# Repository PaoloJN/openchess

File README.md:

<h1 align="center">OpenChess</h1>

<p align="center">
  A chessboard that knows where the pieces are.<br>
  64 Hall sensors, 81 RGB LEDs, one ESP32, a 3D-printed case, and a phone app.<br>
  Designed in KiCad, assembled by JLCPCB and by hand, built once, for one desk.
</p>

<p align="center">
  <a href="STATUS.md">Status</a> ·
  <a href="#how-it-works">How it works</a> ·
  <a href="#repository-map">Repo map</a> ·
  <a href="#build-notes">Build notes</a> ·
  <a href="#licenses">Licenses</a>
</p>

<p align="center">
  
  &nbsp;&nbsp;
  
</p>

---

## What this is

A one-off, hands-on learning project, built during my year-long internship at
UMD CPSE. I had never designed a PCB before this. The goal was never a
product. It was to get one physical board that:

- detects every piece on every square with a magnet under each piece,
- shows legal moves, hints, and errors with LEDs at the square corners,
- plays offline against its own chess engine with a little OLED menu,
- talks to a companion phone app over Bluetooth,
- lives in a clean printed case with a swappable top plate.

The first boards came back from JLCPCB in June 2026 and worked on the first
power-up. Everything since then has been firmware, the case, the app, and a
battery-module swap so it runs without a cable.

## See it work

<p align="center">
  
  &nbsp;&nbsp;&nbsp;
  
</p>

<p align="center">
  <sub>Left: the board under its wooden top, reacting to pieces. Right: first power-up of the bare matrix, one pixel walking the LED chain. Full-quality clip: <a href="docs/media/demo-pieces.mp4">demo-pieces.mp4</a>.</sub>
</p>

## How it works

**Sensing.** Each square has a DRV5032FC Hall-effect sensor under it. The
matrix is scanned one column at a time: the controller powers a column through
a TBD62783A high-side driver, then reads eight row lines. A full scan of the
board takes about 100 ms, fast enough to feel instant.

**Lights.** 81 WS2812B LEDs sit on the 9x9 grid of square corners, so one
square lights up as its four corners. The ESP32 drives the chain through a
74AHCT125 level shifter so the data line is a real 5 V signal. Frames go out
over I2S DMA so flash writes from Bluetooth cannot corrupt them mid-frame.

**Brain.** An ESP32 runs one non-blocking loop: sensor scan, game controller,
LED language, OLED menu, and a BLE server. The offline engine is a homebrew
alpha-beta search with quiescence, iterative deepening, piece-square tables,
and move ordering. It plays at a few selectable strengths and runs its own
native unit tests on the desktop.

**UI.** A 0.91" SSD1306 OLED and three buttons on the front wall of the case
for menus, plus a React Native app that pairs over BLE, mirrors the board,
streams moves, and controls the LEDs.

**Case.** Designed in Fusion 360 around the real PCB STEP exports. The walls
and front panel print as one part, the top plate is swappable between a
two-color printed chessboard and a laser-cut plexi top, and the back cover
clamps the PCB stack with heat-set inserts.

## Where things stand

| Area | State |
|---|---|
| Matrix board v0.1 | Built, all 64 sensors and 81 LEDs verified on hardware |
| Controller v0.1 | Built, works on USB. The stock battery module shuts its boost down under light load, so it is being replaced with a bq25185 charger/boost |
| Controller v2 | Shelved. An integrated ESP32-WROOM-32E, USB-C, charger, and boost design got as far as a clean schematic, then the v0.1 board proved good enough |
| Firmware | Integrated product build: OLED menu, offline AI, coaching lights, BLE. Desktop-tested, hardware verification ongoing |
| Companion app | Expo app, all screens built, real BLE pairing works end to end on an iPhone |
| Case | Final print package exported, corner test piece printed and iterated through v9 |
| Robot arm | Side quest: the board drives a Waveshare RoArm-M2-S over ESP-NOW, with a DIY servo gripper |

The detailed, dated list of next actions lives in [`STATUS.md`](STATUS.md).

## Repository map

```text
openchess/
├── hardware/
│   ├── hardware-board/          8x8 matrix PCB, 282 x 282 mm (KiCad, gerbers, JLC BOM/CPL)
│   ├── hardware-controller/     controller v0.1, DevKitC + Lipo Rider (frozen, boards exist)
│   ├── hardware-controller-v2/  shelved v2 design, schematic only, kept for reference
│   └── DESIGN_NOTES.md          design rationale and history for the v0.1 boards
├── firmware/                    PlatformIO ESP32 firmware: engine, UI, BLE, bench sketches
├── app/                         Expo / React Native companion app (BLE)
├── mechanical/                  Fusion 360 case, print package, plexi top, test pieces
├── firmware-roarm/              vendored RoArm-M2-S firmware with the gripper patch
├── docs/                        GPIO map, connector contracts, BOM, design specs
├── scripts/                     PDF tiling helpers, robot-arm console
└── references/                  upstream projects this builds on (git-ignored clones)
```

## Build notes

**Hardware.** Open the KiCad projects under `hardware/`. The v0.1 boards were
fabricated and SMD-assembled by JLCPCB using the Fabrication Toolkit plugin
exports in each board's `production/` folder. The DevKitC, Lipo Rider, column
driver, and connectors were hand-soldered.

**Firmware.**

```bash
cd firmware
pio run -e esp32dev -t upload      # the integrated product build
pio run -e bench_sensor -t upload  # or any bench sketch from src/bench/
pio test -e native_ai              # engine unit tests on the desktop
```

The GPIO map lives in `firmware/src/pins.h` and `docs/gpio-map.md`. On the
v0.1 controller the OLED shares the UART0 pins, so unplug the OLED to flash.

**App.**

```bash
cd app
npm install
npx expo run:ios        # BLE needs a native dev build, not Expo Go
```

**Case.** Print files and the screw list are in `mechanical/exports/README.md`.
Print the corner test piece first.

## Built on

- [joojoooo/OpenChess](https://github.com/joojoooo/OpenChess): the firmware
  started as an adaptation of this engine and board driver.
- [omercier01/Chessboard](https://github.com/omercier01/Chessboard): the v1
  board this rebuild started from.
- [waveshareteam/roarm_m2](https://github.com/waveshareteam/roarm_m2): the
  robot arm firmware, vendored with a small gripper patch.

## Licenses

| Part | License |
|---|---|
| Hardware (`hardware/`, `mechanical/`) | [CERN-OHL-S v2](LICENSE-hardware) |
| Firmware and app (`firmware/`, `app/`) | [MIT](LICENSE-firmware) |
| Documentation | [CC-BY-4.0](LICENSE-docs) |
| `firmware-roarm/` | Upstream Waveshare license, see its `LICENSE` |

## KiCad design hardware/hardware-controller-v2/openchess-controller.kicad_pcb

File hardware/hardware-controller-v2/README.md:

# hardware-controller-v2 (shelved)

**Status: shelved 2026-10-24, never fabricated.** The schematic reached
ERC-clean and layout was started. Dropped because the v0.1 controller with a
battery-module swap does the job for a one-off board. Kept for reference.

Integrated controller: soldered ESP32-WROOM-32E + USB-C (CH340C) + BQ24074
power-path charger + TPS61022 5V boost + AMS1117-3.3. Replaces the v1
DevKitC + Lipo Rider Plus daughterboards.

- Spec: `docs/superpowers/specs/2026-07-27-controller-v2-integrated-design.md`
- Plan: `docs/superpowers/plans/2026-07-27-controller-v2-integrated.md`
- GPIO map: `docs/gpio-map.md` (v2 table)
- Part sourcing + design values: `SOURCING.md`

The KiCad files keep their original names (`openchess-controller.*`) within this
directory; the directory name itself (`hardware-controller-v2/`) distinguishes v2
from frozen v1.

v1 (`../hardware-controller/`) is frozen — boards exist physically.

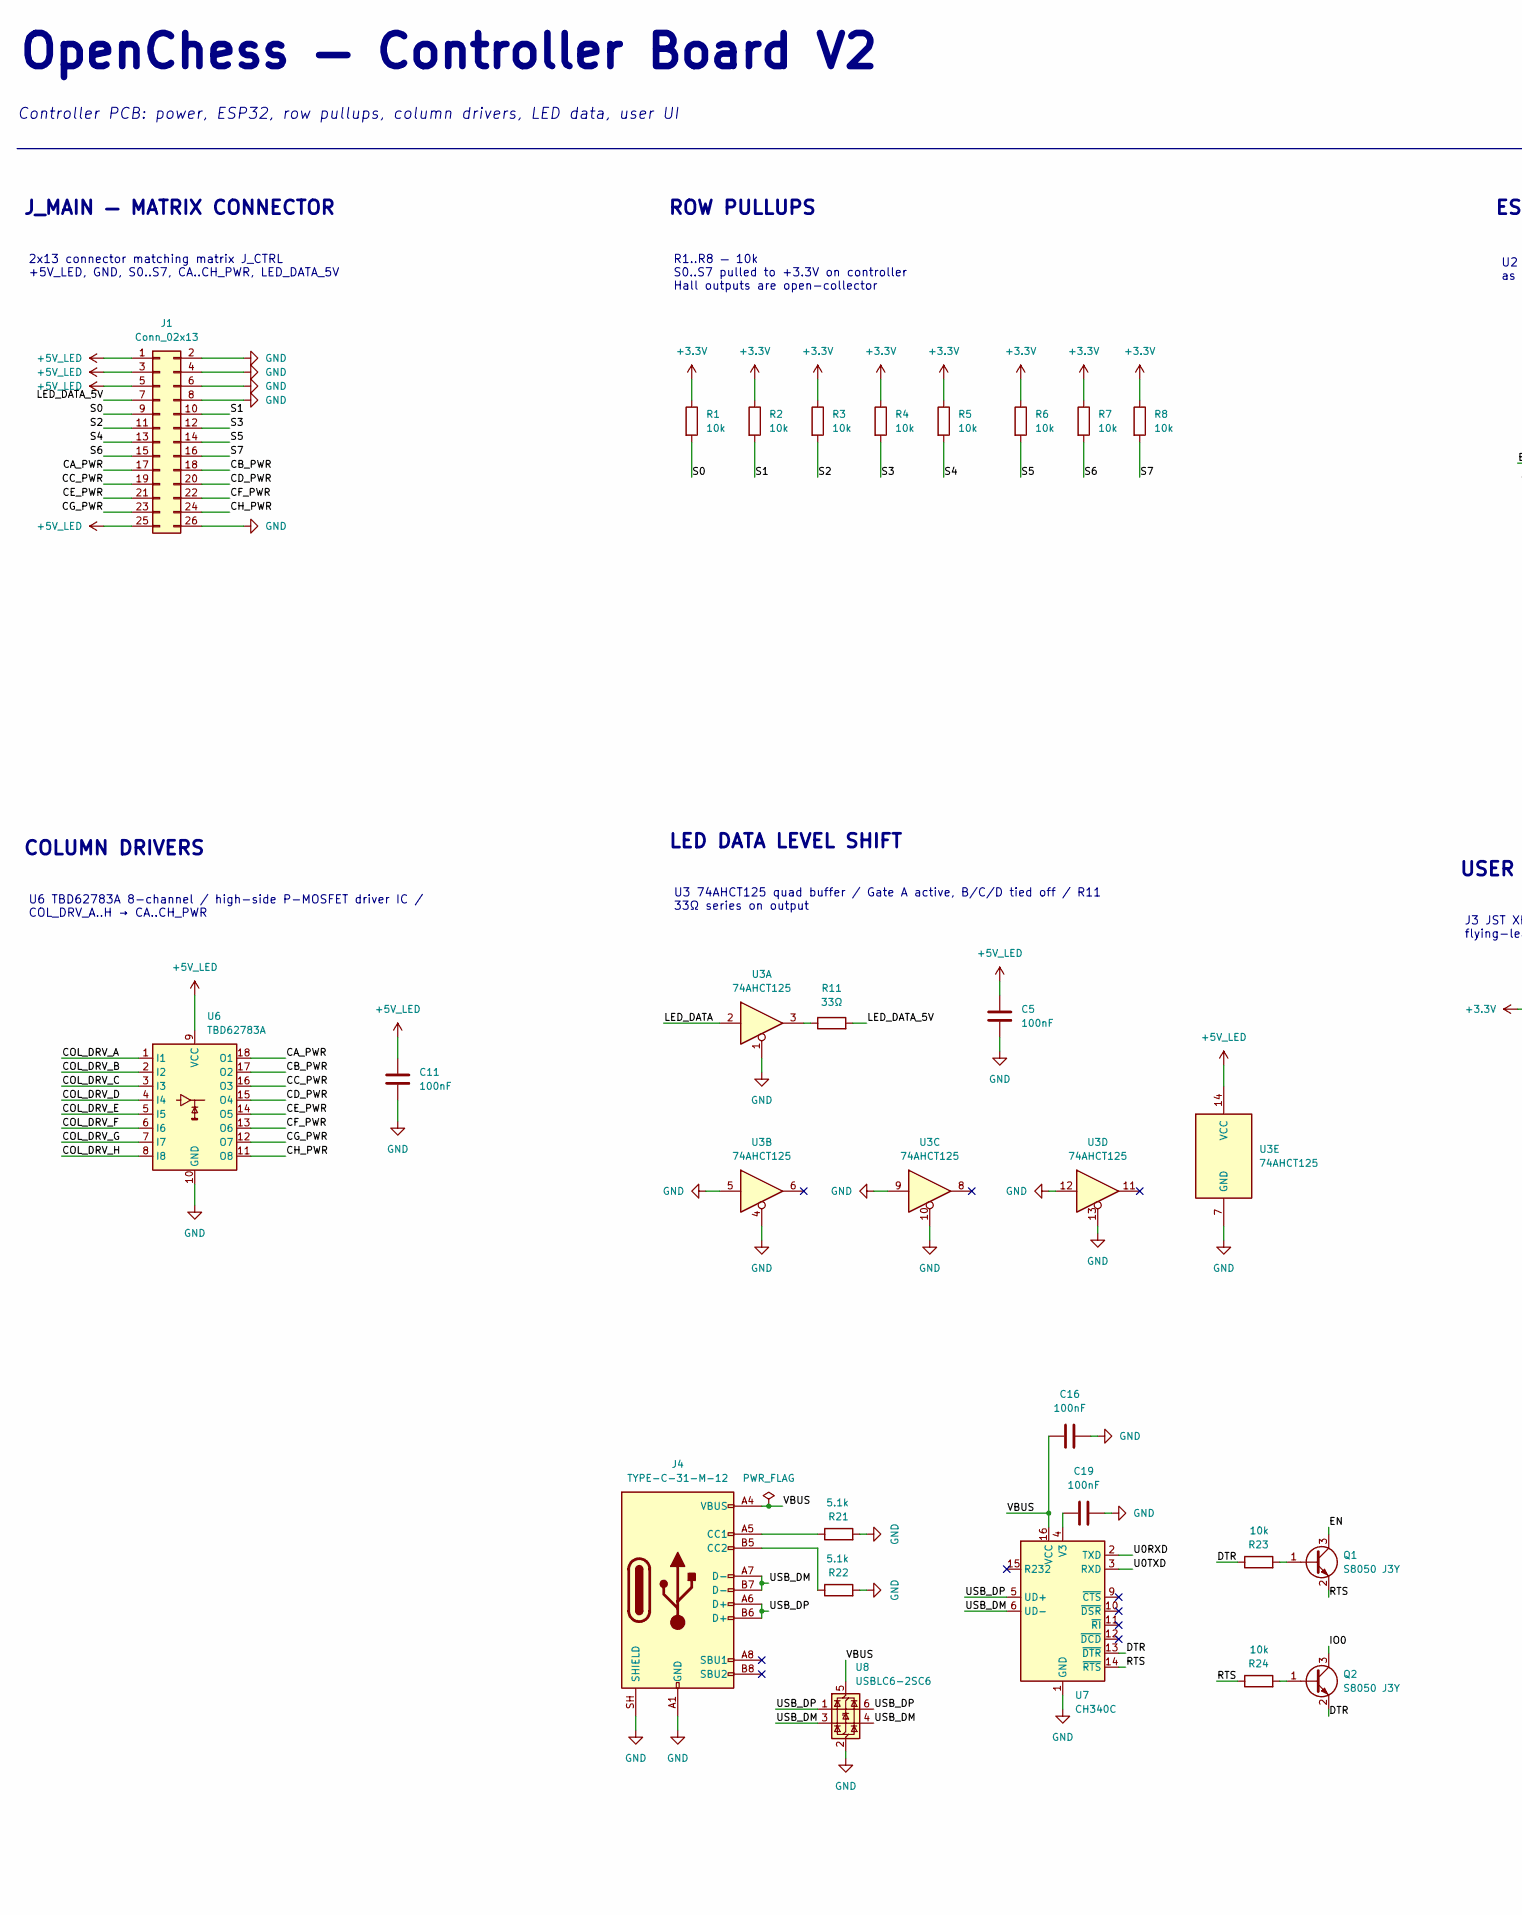
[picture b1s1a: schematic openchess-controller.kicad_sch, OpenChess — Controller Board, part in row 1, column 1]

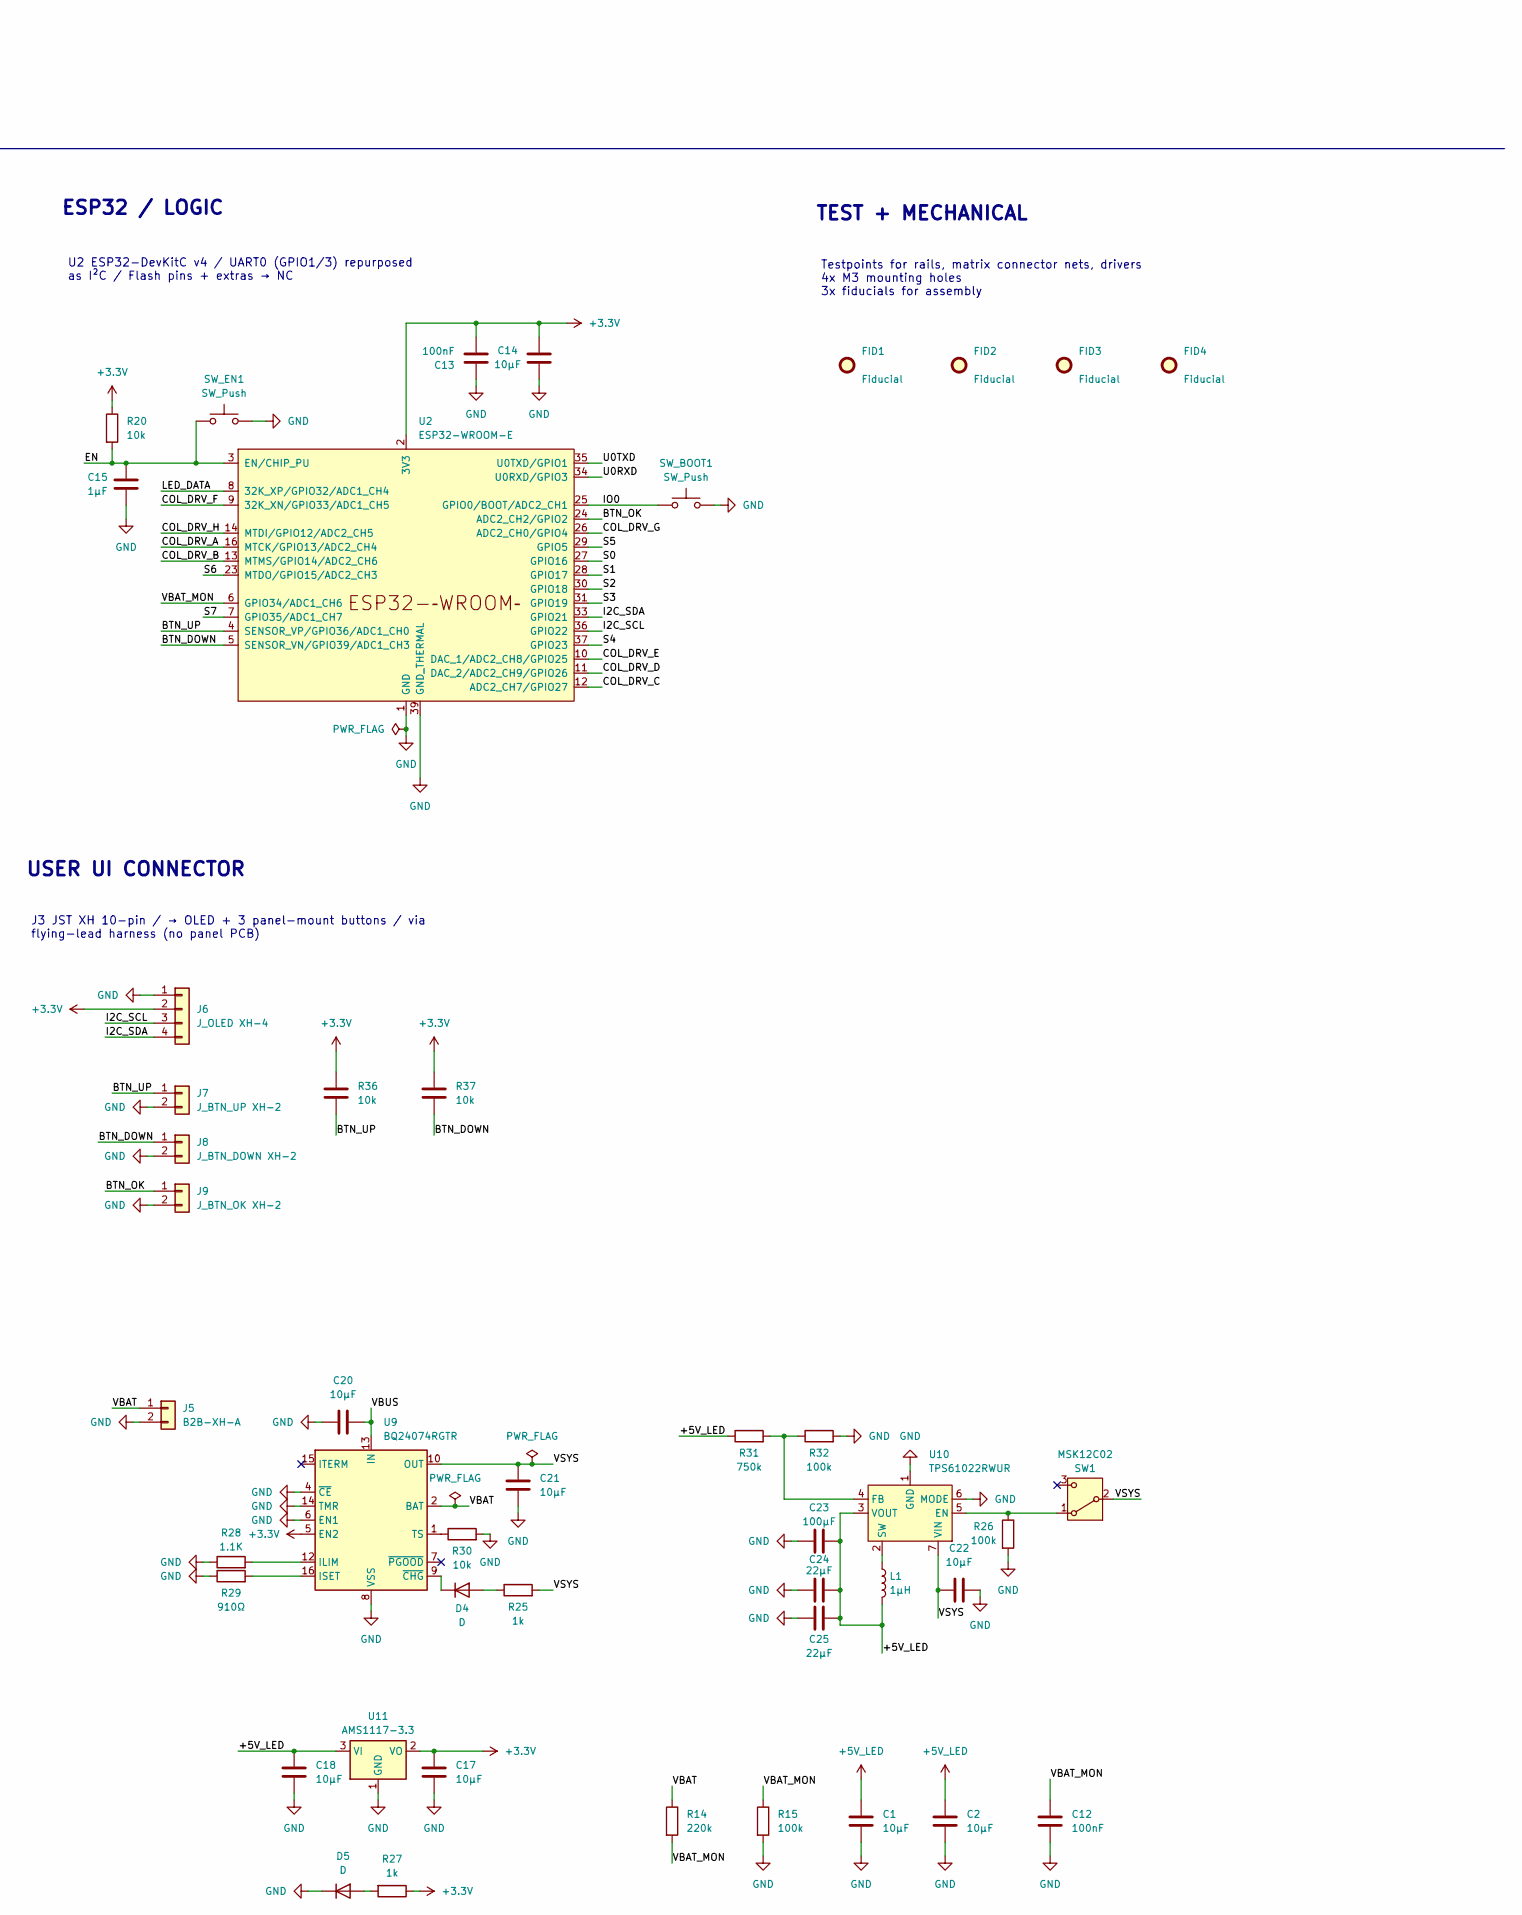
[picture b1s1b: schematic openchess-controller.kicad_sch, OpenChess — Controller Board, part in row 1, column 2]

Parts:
C1, C2, C14, C17, C18, C20, C21, C22: 10µF; C_0805_2012Metric
C5: 100nF; C_0805_2012Metric
C11, C12, C13, C16, C19: 100nF; C_0603_1608Metric
C15: 1µF; C_0603_1608Metric
C23: 100µF; CP_Elec_6.3x5.4
C24, C25: 22µF; C_0805_2012Metric
D4: D; LED_0603_1608Metric; LCSC C2286
D5: D; LED_0603_1608Metric; LCSC C12624
FID1, FID2, FID3, FID4: Fiducial; Fiducial_1mm_Mask2mm
J1: Conn_02x13; PinHeader_2x13_P2.54mm_Vertical
J4: TYPE-C-31-M-12; USB_C_Receptacle_HRO_TYPE-C-31-M-12; LCSC C165948
J5: B2B-XH-A; JST_XH_B2B-XH-A_1x02_P2.50mm_Vertical
J6: J_OLED XH-4; JST_XH_B4B-XH-A_1x04_P2.50mm_Vertical
J7: J_BTN_UP XH-2; JST_XH_B2B-XH-A_1x02_P2.50mm_Vertical
J8: J_BTN_DOWN XH-2; JST_XH_B2B-XH-A_1x02_P2.50mm_Vertical
J9: J_BTN_OK XH-2; JST_XH_B2B-XH-A_1x02_P2.50mm_Vertical
L1: 1µH; L_APV_APH0420; LCSC C5349664
Q1, Q2: S8050 J3Y; SOT-23; LCSC C42441446
R1, R2, R3, R4, R5, R6, R7, R8: 10k; R_0805_2012Metric; LCSC C17414
R11: 33Ω; R_0603_1608Metric; LCSC C23140
R14: 220k; R_0603_1608Metric
R15, R26, R32: 100k; R_0603_1608Metric; LCSC C25803
R20, R23, R24, R30, R36, R37: 10k; R_0603_1608Metric; LCSC C25804
R21, R22: 5.1k; R_0603_1608Metric
R25, R27: 1k; R_0603_1608Metric; LCSC C21190
R28: 1.1K; R_0603_1608Metric; LCSC C22764
R29: 910Ω; R_0603_1608Metric
R31: 750k; R_0603_1608Metric; LCSC C23240
SW1: MSK12C02; SW_SPDT_Shouhan_MSK12C02; LCSC C431540
SW_BOOT1: SW_Push; SW_Push_1P1T_XKB_TS-1187A; LCSC C318884
SW_EN1: SW_Push; SW_Push_1P1T_XKB_TS-1187A; LCSC C318884
U2: ESP32-WROOM-E; ESP32-WROOM-32E; LCSC C701341
U3: 74AHCT125; SOIC-14_3.9x8.7mm_P1.27mm; LCSC C2139
U6: TBD62783A; SOP-18_7.495x11.515mm_P1.27mm; LCSC C97745
U7: CH340C; SOIC-16_3.9x9.9mm_P1.27mm; LCSC C84681
U8: USBLC6-2SC6; SOT-23-6; LCSC C7519
U9: BQ24074RGTR; VQFN-16-1EP_3x3mm_P0.5mm_EP1.6x1.6mm_ThermalVias; LCSC C54313
U10: TPS61022RWUR; Texas_RWU0007A_VQFN-7_2x2mm_P0.5mm; LCSC C915088
U11: AMS1117-3.3; SOT-223-3_TabPin2; LCSC C6186

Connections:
+3.3V: C13.1, C14.2, C17.1, J6.2, R1.1, R2.1, R3.1, R4.1, R5.1, R6.1, R7.1, R8.1, R20.1, R27.1, R36.1, R37.1, U2.2 (3V3), U9.5 (EN2), U11.2 (VO)
+5V_LED: C1.1, C2.1, C5.1, C11.1, C18.1, C23.1, C24.1, C25.1, J1.1, J1.3, J1.5, J1.25, L1.2, R31.1, U3.14 (VCC), U6.9 (VCC), U10.3 (VOUT), U11.3 (VI)
/BTN_DOWN: J8.1, R37.2, U2.5 (SENSOR_VN/GPIO39/ADC1_CH3)
/BTN_OK: J9.1, U2.24 (ADC2_CH2/GPIO2)
/BTN_UP: J7.1, R36.2, U2.4 (SENSOR_VP/GPIO36/ADC1_CH0)
/CA_PWR: J1.17, U6.18 (O1)
/CB_PWR: J1.18, U6.17 (O2)
/CC_PWR: J1.19, U6.16 (O3)
/CD_PWR: J1.20, U6.15 (O4)
/CE_PWR: J1.21, U6.14 (O5)
/CF_PWR: J1.22, U6.13 (O6)
/CG_PWR: J1.23, U6.12 (O7)
/CH_PWR: J1.24, U6.11 (O8)
/COL_DRV_A: U2.16 (MTCK/GPIO13/ADC2_CH4), U6.1 (I1)
/COL_DRV_B: U2.13 (MTMS/GPIO14/ADC2_CH6), U6.2 (I2)
/COL_DRV_C: U2.12 (ADC2_CH7/GPIO27), U6.3 (I3)
/COL_DRV_D: U2.11 (DAC_2/ADC2_CH9/GPIO26), U6.4 (I4)
/COL_DRV_E: U2.10 (DAC_1/ADC2_CH8/GPIO25), U6.5 (I5)
/COL_DRV_F: U2.9 (32K_XN/GPIO33/ADC1_CH5), U6.6 (I6)
/COL_DRV_G: U2.26 (ADC2_CH0/GPIO4), U6.7 (I7)
/COL_DRV_H: U2.14 (MTDI/GPIO12/ADC2_CH5), U6.8 (I8)
/DTR: Q2.2 (E), R23.1, U7.13 (~DTR)
/EN: C15.1, Q1.3 (C), R20.2, SW_EN1.1, U2.3 (EN/CHIP_PU)
/I2C_SCL: J6.3, U2.36 (GPIO22)
/I2C_SDA: J6.4, U2.33 (GPIO21)
/IO0: Q2.3 (C), SW_BOOT1.1, U2.25 (GPIO0/BOOT/ADC2_CH1)
/LED_DATA: U2.8 (32K_XP/GPIO32/ADC1_CH4), U3.2
/LED_DATA_5V: J1.7, R11.2
/RTS: Q1.2 (E), R24.1, U7.14 (~RTS)
/S0: J1.9, R1.2, U2.27 (GPIO16)
/S1: J1.10, R2.2, U2.28 (GPIO17)
/S2: J1.11, R3.2, U2.30 (GPIO18)
/S3: J1.12, R4.2, U2.31 (GPIO19)
/S4: J1.13, R5.2, U2.37 (GPIO23)
/S5: J1.14, R6.2, U2.29 (GPIO5)
/S6: J1.15, R7.2, U2.23 (MTDO/GPIO15/ADC2_CH3)
/S7: J1.16, R8.2, U2.7 (GPIO35/ADC1_CH7)
/U0RXD: U2.34 (U0RXD/GPIO3), U7.2 (TXD)
/U0TXD: U2.35 (U0TXD/GPIO1), U7.3 (RXD)
/USB_DM: J4.A7 (D-), J4.B7 (D-), U7.6 (UD-), U8.3 (I/O2), U8.4 (I/O2)
/USB_DP: J4.A6 (D+), J4.B6 (D+), U7.5 (UD+), U8.1 (I/O1), U8.6 (I/O1)
/VBAT: J5.1, R14.1, U9.2 (BAT), U9.3 (BAT)
/VBAT_MON: C12.1, R14.2, R15.1, U2.6 (GPIO34/ADC1_CH6)
/VBUS: C16.1, C20.2, J4.A4 (VBUS), J4.A9 (VBUS), J4.B4 (VBUS), J4.B9 (VBUS), U7.16 (VCC), U8.5 (VBUS), U9.13 (IN)
/VSYS: C21.2, C22.2, R25.2, SW1.2 (B), U9.10 (OUT), U9.11 (OUT), U10.7 (VIN)
GND: C1.2, C2.2, C5.2, C11.2, C12.2, C13.2, C14.1, C15.2, C16.2, C17.2, C18.2, C19.2, C20.1, C21.1, C22.1, C23.2, C24.2, C25.2, D5.1 (K), J1.2, J1.4, J1.6, J1.8, J1.26, J4.A1 (GND), J4.A12 (GND), J4.B1 (GND), J4.B12 (GND), J4.SH (SHIELD), J5.2, J6.1, J7.2, J8.2, J9.2, R15.2, R21.2, R22.2, R26.2, R28.1, R29.1, R30.2, R32.2, SW_BOOT1.2, SW_EN1.2, U2.1 (GND), U2.15 (GND), U2.38 (GND), U2.39 (GND_THERMAL), U3.1, U3.4, U3.5, U3.7 (GND), U3.9, U3.10, U3.12, U3.13, U6.10 (GND), U7.1 (GND), U8.2 (GND), U9.4 (~CE), U9.6 (EN1), U9.8 (VSS), U9.14 (TMR), U9.17 (VSS), U10.1 (GND), U10.6 (MODE), U11.1 (GND)
unnamed: D4.2 (A), R25.1
unnamed: D4.1 (K), U9.9 (~CHG)
unnamed: D5.2 (A), R27.2
unnamed: J4.A5 (CC1), R21.1
unnamed: J4.B5 (CC2), R22.1
unnamed: Q1.1 (B), R23.2
unnamed: Q2.1 (B), R24.2
unnamed: R11.1, U3.3
unnamed: R26.1, SW1.1 (A), U10.5 (EN)
unnamed: C19.1, U7.4 (V3)
unnamed: R28.2, U9.12 (ILIM)
unnamed: R29.2, U9.16 (ISET)
unnamed: R30.1, U9.1 (TS)
unnamed: R31.2, R32.1, U10.4 (FB)
unnamed: L1.1, U10.2 (SW)

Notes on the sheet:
OpenChess — Controller Board V2
Controller PCB: power, ESP32, row pullups, column drivers, LED data, user UI
J_MAIN — MATRIX CONNECTOR
2x13 connector matching matrix J_CTRL +5V_LED, GND, S0..S7, CA..CH_PWR, LED_DATA_5V
ROW PULLUPS
R1..R8 — 10k S0..S7 pulled to +3.3V on controller Hall outputs are open-collector
ESP32 / LOGIC
U2 ESP32-DevKitC v4 / UART0 (GPIO1/3) repurposed as I²C / Flash pins + extras → NC
COLUMN DRIVERS
U6 TBD62783A 8-channel / high-side P-MOSFET driver IC / COL_DRV_A..H → CA..CH_PWR
LED DATA LEVEL SHIFT
U3 74AHCT125 quad buffer / Gate A active, B/C/D tied off / R11 33Ω series on output
USER UI CONNECTOR
J3 JST XH 10-pin / → OLED + 3 panel-mount buttons / via flying-lead harness (no panel PCB)
TEST + MECHANICAL
Testpoints for rails, matrix connector nets, drivers 4x M3 mounting holes 3x fiducials for assembly

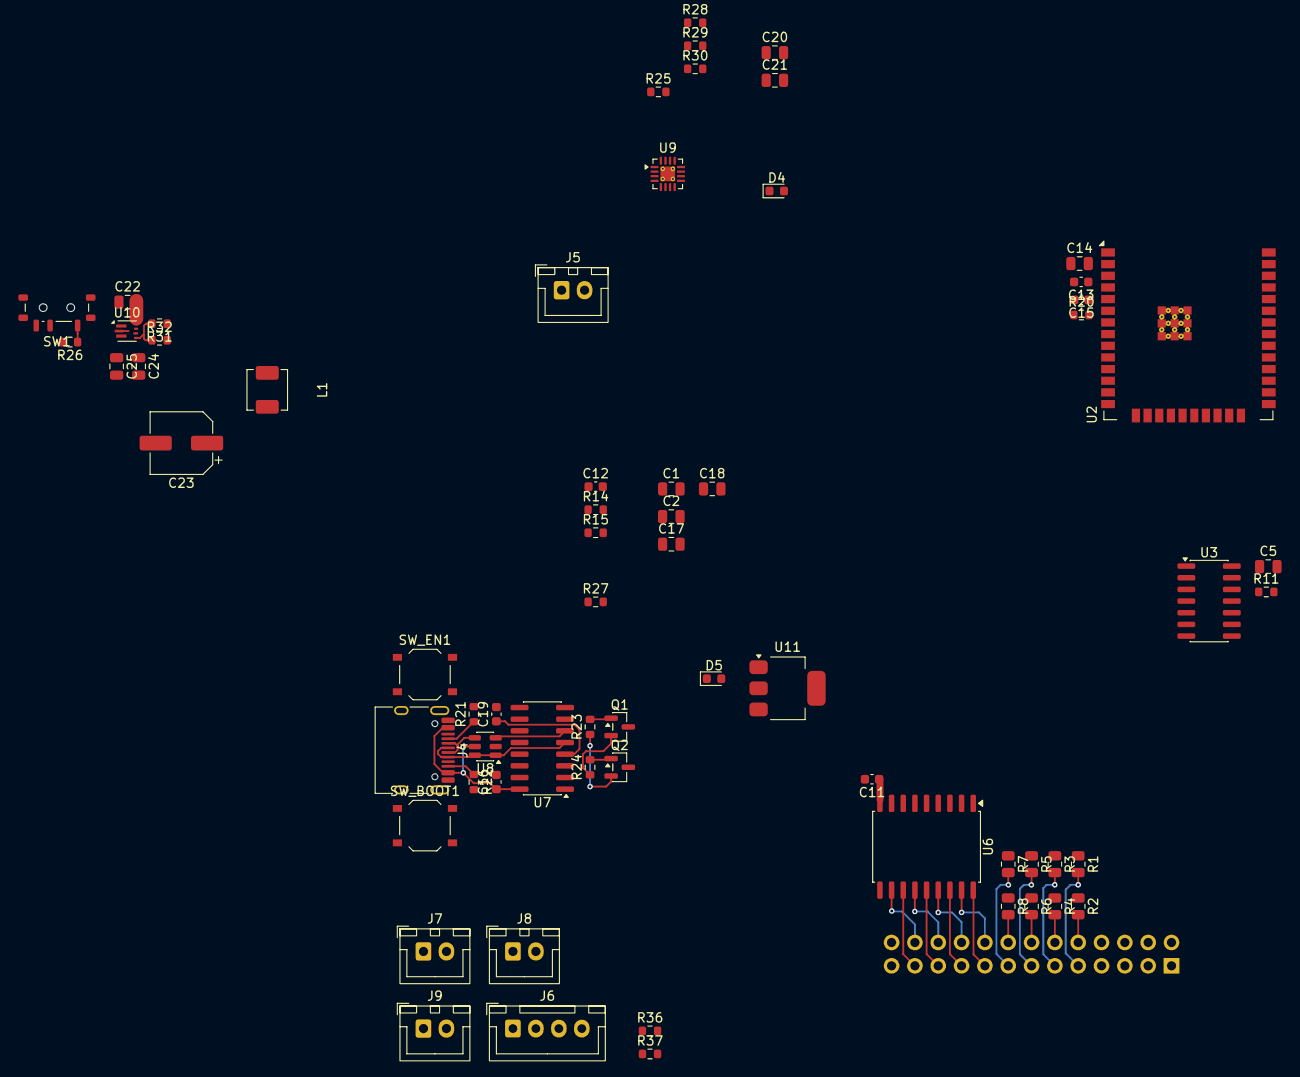
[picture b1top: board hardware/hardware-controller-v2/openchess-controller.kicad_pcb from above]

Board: 2 copper layers, 67 parts (1 on the bottom side), 61 nets.

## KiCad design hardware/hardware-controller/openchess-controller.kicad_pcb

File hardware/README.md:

# OpenChess Hardware

One KiCad project per board. v0.1 is what exists; v2 is a shelved design.

```text
hardware-board/          8x8 matrix PCB, 282 x 282 mm. Built and verified.
hardware-controller/     controller v0.1, 58 x 71 mm. Built. Frozen, boards exist.
hardware-controller-v2/  shelved v2 design: integrated ESP32 + USB-C + charger + boost. Schematic only.
DESIGN_NOTES.md          design rationale and history for the v0.1 boards
```

Each built board directory carries its KiCad files, `scripts/` for generated
placement and routing, `production/` with the Fabrication Toolkit exports that
went to JLCPCB, and `gerbers/`.

Connector contracts are in `../docs/inter-board-connector.md`, the GPIO map in
`../docs/gpio-map.md`. The v2 folder keeps its own `README.md` and
`SOURCING.md` in case the idea is ever picked back up.

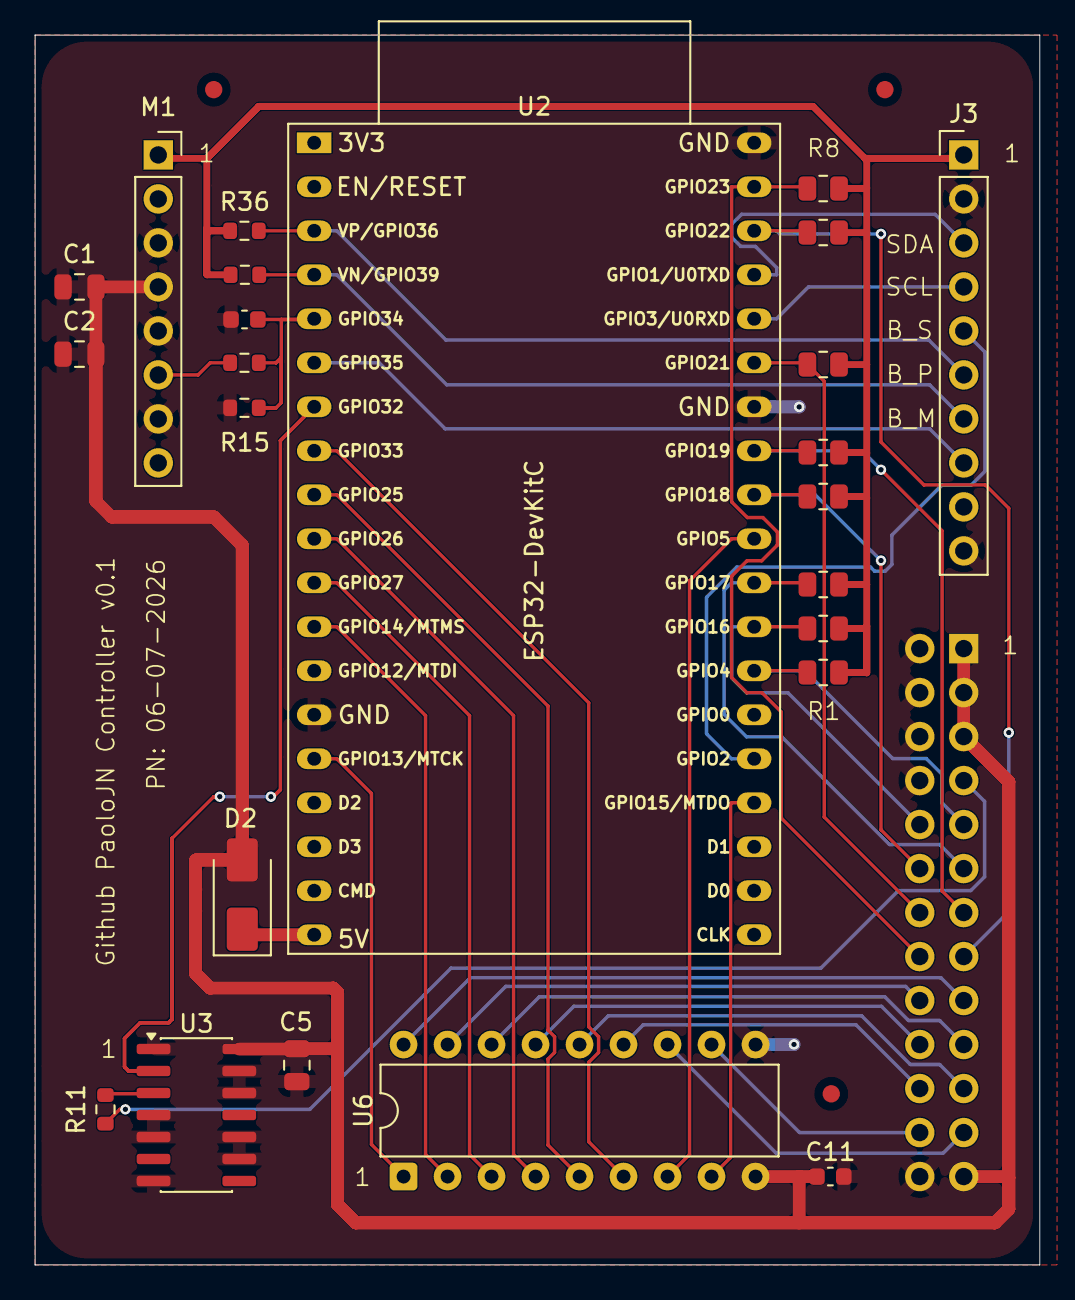
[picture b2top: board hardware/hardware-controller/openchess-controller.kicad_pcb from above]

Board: 2 copper layers, 58.0 x 71.0 mm, 28 parts (1 on the bottom side), 39 nets.

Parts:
C1, C2: 10µF; C_0805_2012Metric
C5: 100nF; C_0805_2012Metric
C11, C12: 100nF; C_0603_1608Metric
D2: SS14 (or BAT60A); D_SMA
FID1, FID2, FID3: Fiducial; Fiducial_1mm_Mask2mm
J1: Conn_02x13; PinHeader_2x13_P2.54mm_Vertical
J3: J_PANEL XH-10; PinHeader_1x10_P2.54mm_Vertical
M1: Lipo Rider Plus; PinSocket_1x08_P2.54mm_Vertical
R1, R2, R3, R4, R5, R6, R7, R8: 10k; R_0805_2012Metric
R11: 33Ω; R_0603_1608Metric
R14: 220k; R_0603_1608Metric
R15: 100k; R_0603_1608Metric
R36, R37: 10k; R_0603_1608Metric
U2: ESP32-DevKitC
U3: 74AHCT125; SOIC-14_3.9x8.7mm_P1.27mm
U6: TBD62783A; DIP-18_W7.62mm

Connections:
+3.3V: J3.1, M1.1, R1.1, R2.1, R3.1, R4.1, R5.1, R6.1, R7.1, R8.1, R36.1, R37.1
+5V_LED: C1.1, C2.1, C5.1, C11.1, D2.2 (A), J1.1, J1.3, J1.5, J1.25, M1.4, U3.14 (VCC), U6.9 (VCC)
/BAT: M1.6, R14.1
/BTN_MODE: J3.7, R37.2, U2.4 (SENSOR_VN/GPIO39/ADC1_CH3)
/BTN_POWER: J3.6, R36.2, U2.3 (SENSOR_VP/GPIO36/ADC1_CH0)
/BTN_SELECT: J3.5, U2.24 (ADC2_CH2/GPIO2)
/CA_PWR: J1.17, U6.18 (O1)
/CB_PWR: J1.18, U6.17 (O2)
/CC_PWR: J1.19, U6.16 (O3)
/CD_PWR: J1.20, U6.15 (O4)
/CE_PWR: J1.21, U6.14 (O5)
/CF_PWR: J1.22, U6.13 (O6)
/CG_PWR: J1.23, U6.12 (O7)
/CH_PWR: J1.24, U6.11 (O8)
/COL_DRV_A: U2.15 (MTCK/GPIO13/ADC2_CH4), U6.1 (I1)
/COL_DRV_B: U2.12 (MTMS/GPIO14/ADC2_CH6), U6.2 (I2)
/COL_DRV_C: U2.11 (ADC2_CH7/GPIO27), U6.3 (I3)
/COL_DRV_D: U2.10 (DAC_2/ADC2_CH9/GPIO26), U6.4 (I4)
/COL_DRV_E: U2.9 (DAC_1/ADC2_CH8/GPIO25), U6.5 (I5)
/COL_DRV_F: U2.8 (32K_XN/GPIO33/ADC1_CH5), U6.6 (I6)
/COL_DRV_G: U2.29 (GPIO5), U6.7 (I7)
/COL_DRV_H: U2.23 (MTDO/GPIO15/ADC2_CH3), U6.8 (I8)
/I2C_SCL: J3.4, U2.34 (U0RXD/GPIO3)
/I2C_SDA: J3.3, U2.35 (U0TXD/GPIO1)
/LED_DATA: U2.7 (32K_XP/GPIO32/ADC1_CH4), U3.2
/LED_DATA_5V: J1.7, R11.2
/PANEL_SPARE: J3.8, U2.6 (VDET_2/GPIO35/ADC1_CH7)
/S0: J1.9, R1.2, U2.26 (ADC2_CH0/GPIO4)
/S1: J1.10, R2.2, U2.27 (GPIO16)
/S2: J1.11, R3.2, U2.28 (GPIO17)
/S3: J1.12, R4.2, U2.30 (GPIO18)
/S4: J1.13, R5.2, U2.31 (GPIO19)
/S5: J1.14, R6.2, U2.33 (GPIO21)
/S6: J1.15, R7.2, U2.36 (GPIO22)
/S7: J1.16, R8.2, U2.37 (GPIO23)
/VBAT_MON: C12.1, R14.2, R15.1, U2.5 (VDET_1/GPIO34/ADC1_CH6)
GND: C1.2, C2.2, C5.2, C11.2, C12.2, J1.2, J1.4, J1.6, J1.8, J1.26, J3.2, J3.10, M1.3, M1.5, M1.7, R15.2, U2.14 (GND), U2.32 (GND), U2.38 (GND), U3.1, U3.4, U3.5, U3.7 (GND), U3.9, U3.10, U3.12, U3.13, U6.10 (GND)
unnamed: D2.1 (K), U2.19 (5V)
unnamed: R11.1, U3.3

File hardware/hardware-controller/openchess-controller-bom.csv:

"Reference","Value","Datasheet","Footprint","Qty","DNP"
"BT1","LiPo 1S 3.7V (protected)","","","1",""
"C1,C2","10µF","","Capacitor_SMD:C_0805_2012Metric","2",""
"C5,C11,C12","100nF","","Capacitor_SMD:C_0603_1608Metric,Capacitor_SMD:C_0805_2012Metric","3",""
"D2","SS14 (or BAT60A)","","Diode_SMD:D_SMA","1",""
"FID1,FID2,FID3,FID4","Fiducial","","Fiducial:Fiducial_1mm_Mask2mm","4",""
"J1","Conn_02x13","","Connector_PinHeader_2.54mm:PinHeader_2x13_P2.54mm_Vertical","1",""
"J3","J_PANEL XH-10","","Connector_PinHeader_2.54mm:PinHeader_1x10_P2.54mm_Vertical","1",""
"M1","Lipo Rider Plus","","Connector_PinSocket_2.54mm:PinSocket_1x08_P2.54mm_Vertical","1",""
"R1,R2,R3,R4,R5,R6,R7,R8,R36,R37","10k","","Resistor_SMD:R_0603_1608Metric,Resistor_SMD:R_0805_2012Metric","10",""
"R11","33Ω","","Resistor_SMD:R_0603_1608Metric","1",""
"R14","220k","","Resistor_SMD:R_0603_1608Metric","1",""
"R15","100k","","Resistor_SMD:R_0603_1608Metric","1",""
"U2","ESP32-DevKitC","https://docs.espressif.com/projects/esp-idf/zh_CN/latest/esp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","Espressif:ESP32-DevKitC","1",""
"U3","74AHCT125","https://www.ti.com/lit/ds/symlink/sn74ahct125.pdf","Package_SO:SOIC-14_3.9x8.7mm_P1.27mm","1",""
"U6","TBD62783A","http://toshiba.semicon-storage.com/info/docget.jsp?did=30523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","Package_DIP:DIP-18_W7.62mm","1",""
